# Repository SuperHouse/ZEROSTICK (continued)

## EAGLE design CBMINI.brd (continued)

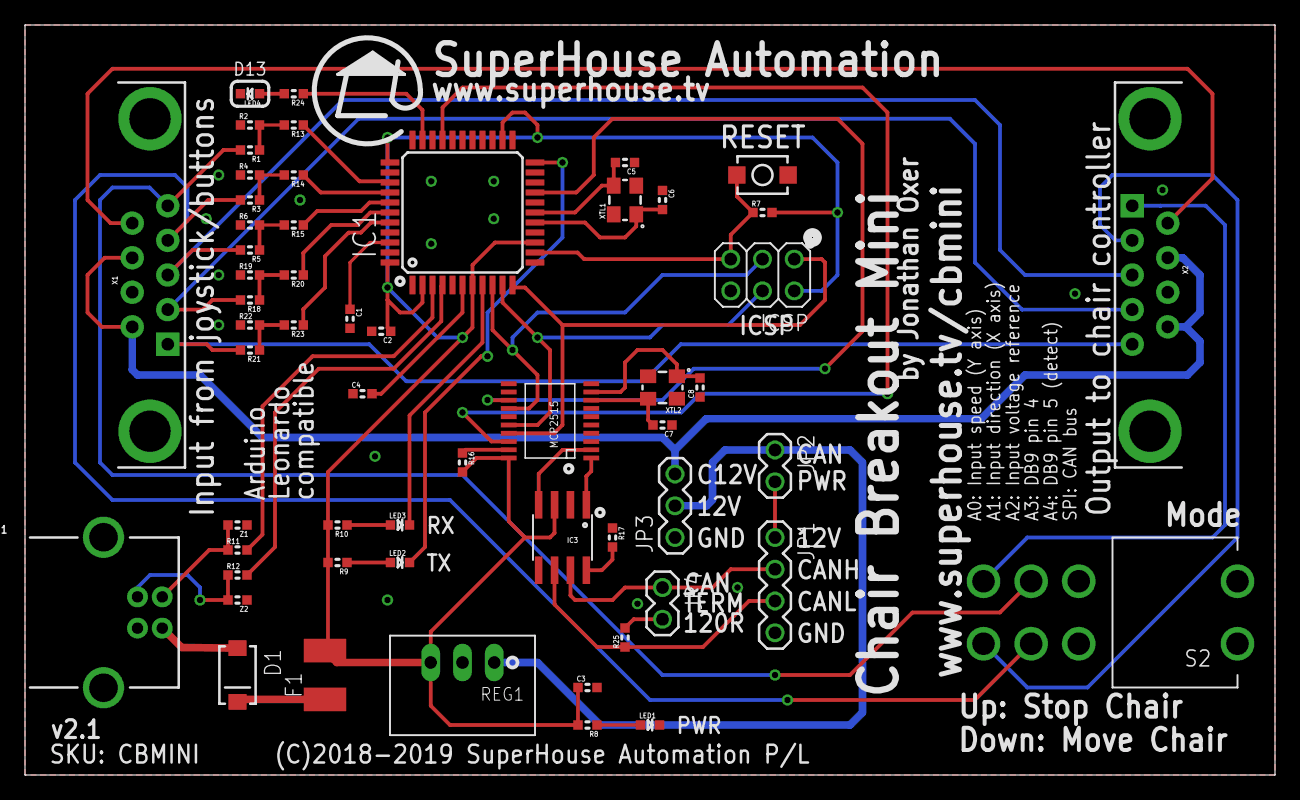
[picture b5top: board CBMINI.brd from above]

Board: 2 copper layers, 100.0 x 60.0 mm, 57 parts (0 on the bottom side), 55 nets.

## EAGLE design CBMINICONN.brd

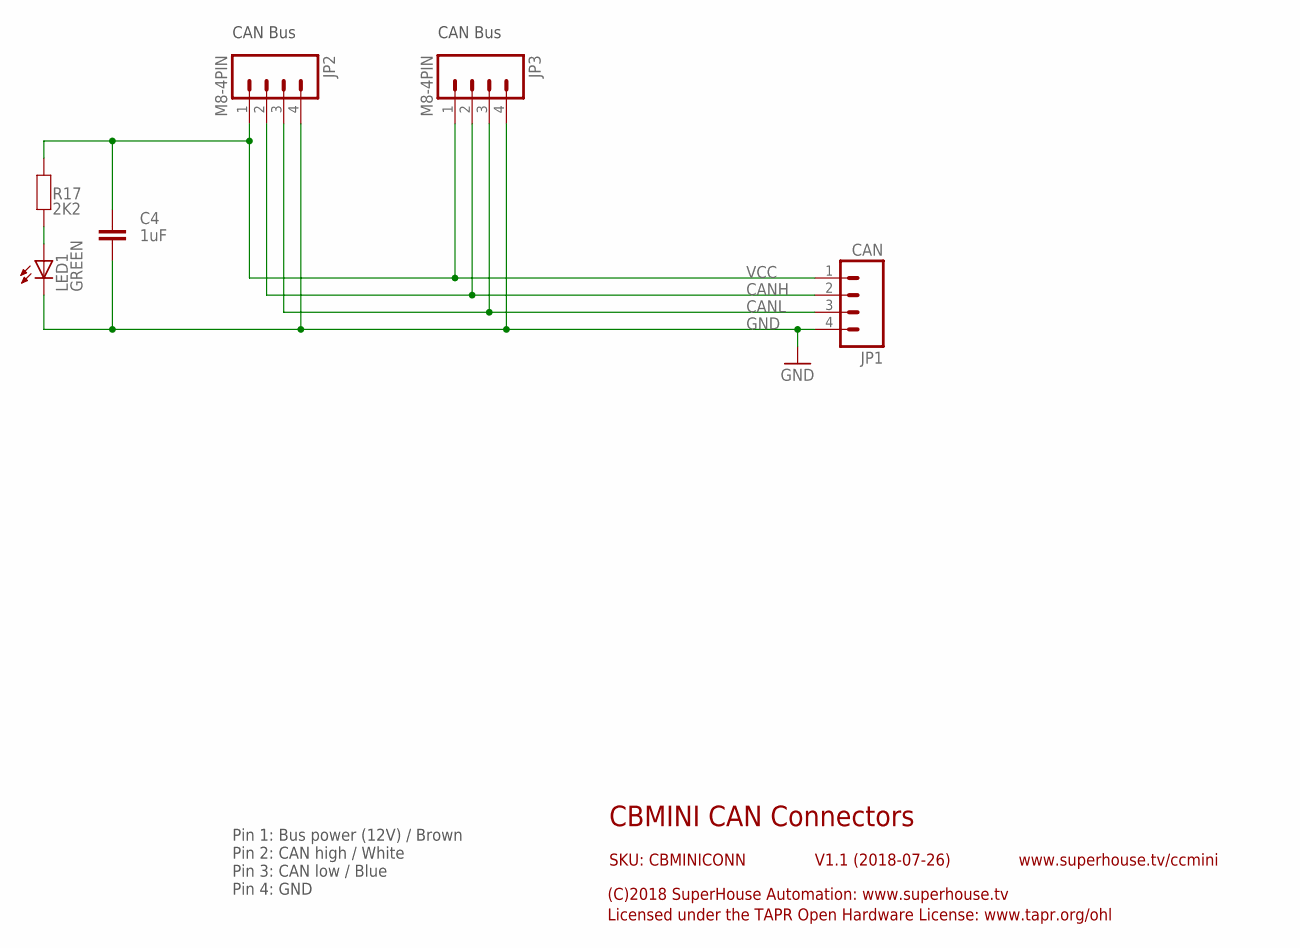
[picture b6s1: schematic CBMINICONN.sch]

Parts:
C4: 1uF; 0603
JP1: CAN; 1X04
JP2, JP3: M8-4PIN
LED1: GREEN; LED3MM
R17: 2K2; 0603

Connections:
CANH: JP1.2, JP2.2, JP3.2
CANL: JP1.3, JP2.3, JP3.3
GND: C4.1, JP1.4, JP2.4, JP3.4, LED1.K (C)
unnamed: LED1.A, R17.1
VCC: C4.2, JP1.1, JP2.1, JP3.1, R17.2

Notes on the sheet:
CBMINI CAN Connectors
V1.1 (2018-07-26)
SKU: CBMINICONN
(C)2018 SuperHouse Automation: www.superhouse.tv
Licensed under the TAPR Open Hardware License: www.tapr.org/ohl
www.superhouse.tv/ccmini
Pin 1: Bus power (12V) / Brown Pin 2: CAN high / White Pin 3: CAN low / Blue Pin 4: GND
CAN Bus

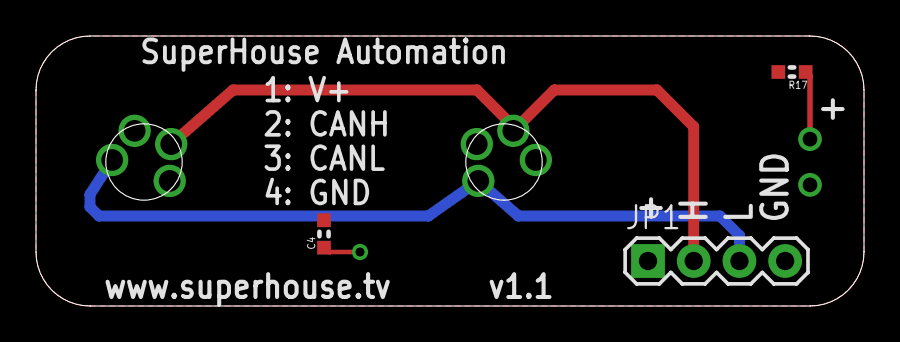
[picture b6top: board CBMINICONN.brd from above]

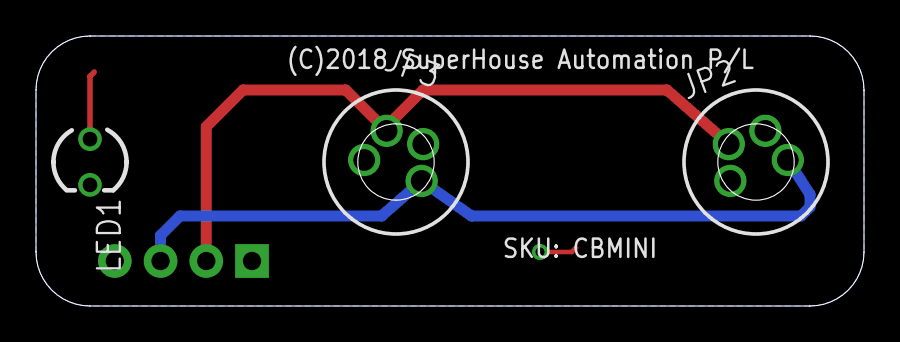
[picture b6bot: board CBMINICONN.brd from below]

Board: 2 copper layers, 46.0 x 15.0 mm, 6 parts (3 on the bottom side), 5 nets.

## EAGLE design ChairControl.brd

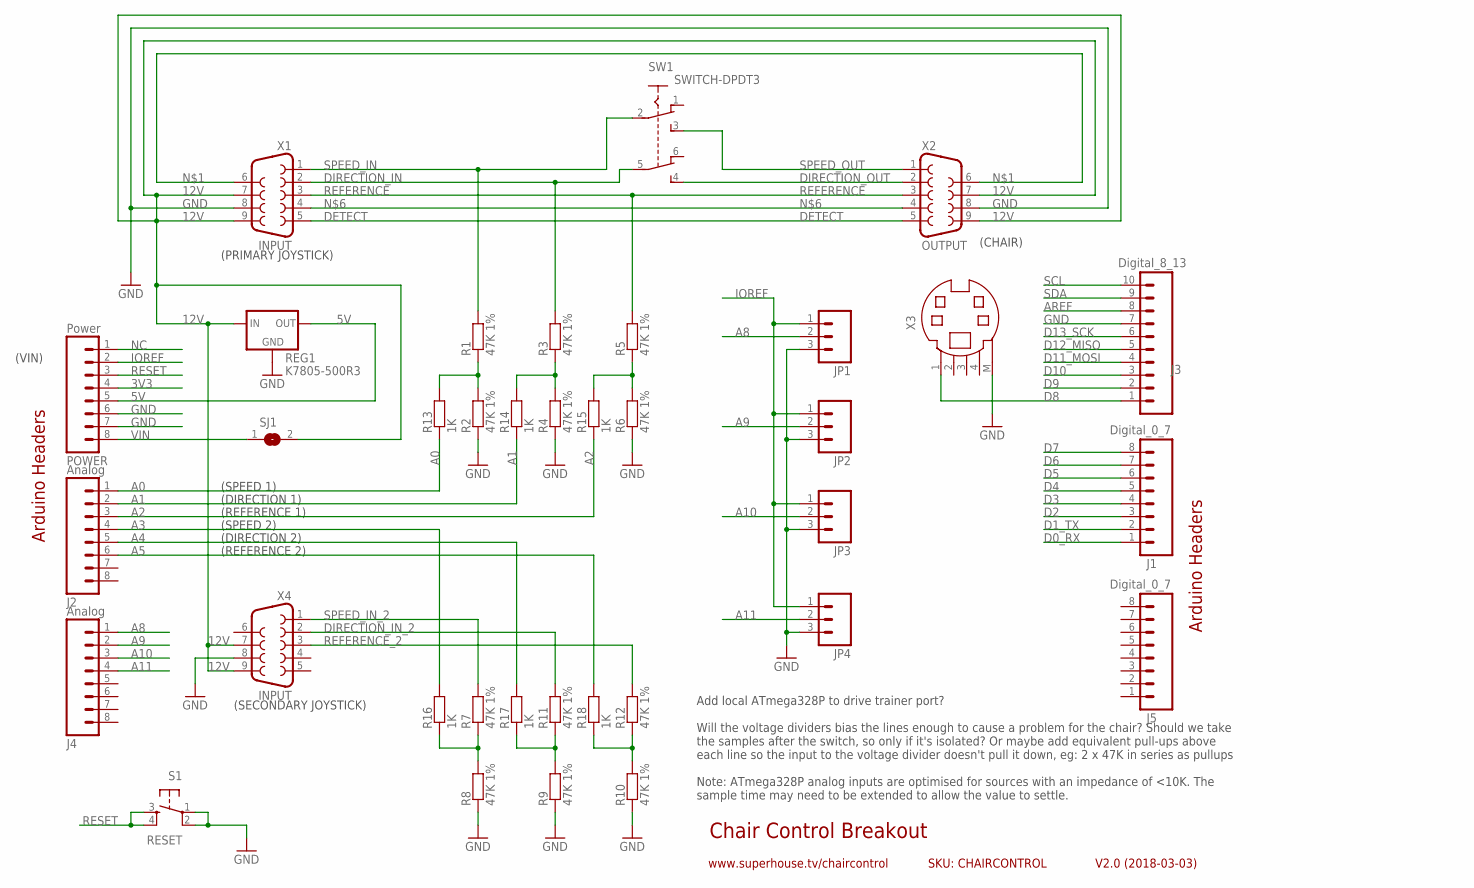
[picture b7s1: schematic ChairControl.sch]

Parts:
J1, J5: Digital_0_7; 1X08
J2, J4: Analog; 1X08
J3: Digital_8_13; 1X10
JP1, JP2, JP3, JP4: M03PTH; 1X03
POWER: Power; 1X08
R1, R2, R3, R4, R5, R6, R7, R8, R9, R10, R11, R12: 47K 1%; 0603
R13, R14, R15, R16, R17, R18: 1K; 0603
REG1: K7805-500R3; K78XX-500R3
S1: RESET; TACTILE-PTH
SJ1: SJN; SJ
SW1: SWITCH-DPDT3; 7201SD9AV2BE
X1, X4: INPUT; DB9_MALE
X2: OUTPUT; DB9
X3: MD04S; MDIN04S

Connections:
3V3: POWER.4
5V: POWER.5, REG1.3 (OUT)
12V: REG1.1 (IN), SJ1.2, X1.7, X1.9, X2.7, X2.9, X4.7, X4.9
A0: J2.1, R13.1
A1: J2.2, R14.1
A2: J2.3, R15.1
A3: J2.4, R16.2
A4: J2.5, R17.2
A5: J2.6, R18.2
A8: J4.1, JP1.2
A9: J4.2, JP2.2
A10: J4.3, JP3.2
A11: J4.4, JP4.2
AREF: J3.8
D0_RX: J1.1
D1_TX: J1.2
D2: J1.3
D3: J1.4
D4: J1.5
D5: J1.6
D6: J1.7
D7: J1.8
D8: J3.1, X3.1
D9: J3.2
D10: J3.3
D11_MOSI: J3.4
D12_MISO: J3.5
D13_SCK: J3.6
DETECT: X1.5, X2.5
DIRECTION_IN: R3.2, SW1.5, X1.2
DIRECTION_IN_2: R11.2, X4.2
DIRECTION_OUT: SW1.4, X2.2
GND: J3.7, JP1.3, JP2.3, JP3.3, JP4.3, POWER.6, POWER.7, R2.1, R4.1, R6.1, R8.1, R9.1, R10.1, REG1.2 (GND), S1.1, S1.2, X1.8, X2.8, X3.M (5), X4.8
IOREF: JP1.1, JP2.1, JP3.1, JP4.1, POWER.2
unnamed: X1.6, X2.6
unnamed: R1.1, R2.2, R13.2
unnamed: R3.1, R4.2, R14.2
unnamed: R5.1, R6.2, R15.2
unnamed: X1.4, X2.4
unnamed: R7.1, R8.2, R16.1
unnamed: R9.2, R11.1, R17.1
unnamed: R10.2, R12.1, R18.1
NC: POWER.1
REFERENCE: R5.2, X1.3, X2.3
REFERENCE_2: R12.2, X4.3
RESET: POWER.3, S1.3, S1.4
SCL: J3.10
SDA: J3.9
SPEED_IN: R1.2, SW1.2, X1.1
SPEED_IN_2: R7.2, X4.1
SPEED_OUT: SW1.3, X2.1
VIN: POWER.8, SJ1.1

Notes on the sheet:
Chair Control Breakout
V2.0 (2018-03-03)
www.superhouse.tv/chaircontrol
SKU: CHAIRCONTROL
Arduino Headers
(PRIMARY JOYSTICK)
(CHAIR)
(VIN)
(SECONDARY JOYSTICK)
Add local ATmega328P to drive trainer port? Will the voltage dividers bias the lines enough to cause a problem for the chair? Should we take the samples after the switch, so only if it's isolated? Or maybe add equivalent pull-ups above each line so the input to the voltage divider doesn't pull it d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
(SPEED 1)
(SPEED 2)
(DIRECTION 1)
(DIRECTION 2)
(REFERENCE 1)
(REFERENCE 2)

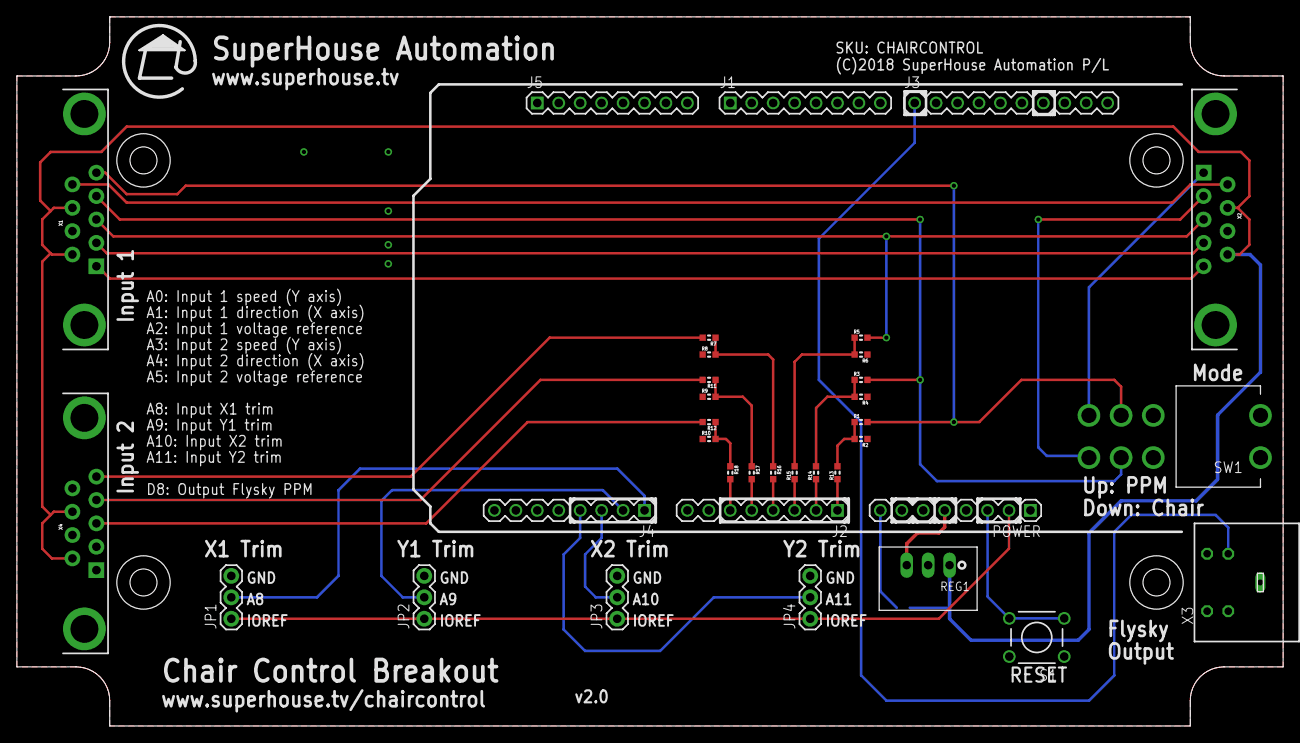
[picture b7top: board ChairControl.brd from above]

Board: 2 copper layers, 150.0 x 84.0 mm, 36 parts (1 on the bottom side), 34 nets.

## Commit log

2018-02-06 Initial project import
2018-02-06 Added Mini DIN-4 connector for Flysky trainer cable connection
2018-02-07 Added second joystick input and changed outline to suit HB5922 case
2018-02-07 Moved Arduino headers to correct location and adjusted connector positions
2018-02-08 Routing and silkscreen
2018-02-08 Added README
2018-02-08 DRC and generated gerbers for v1.0 release
2018-03-03 Added trim inputs and extra headers for Mega footprint
2018-03-27 Improved silkscreen
2018-07-10 Isolated 12V power from passthrough to allow separate power source
2018-07-10 Forked project files for Mini version
2018-07-10 Added CAN interface and removed second joystick input
2018-07-12 Added power source selection and DRC for v1.0 release
2018-07-18 Renamed project files to match SKU
2018-07-23 Improved designators
2018-07-26 Added CAN bus interrupt connection to D2 for v1.1 release
2018-07-27 Changed CAN crystal to 16MHz for compatibility with Arduino CAN shields
2018-07-27 Added connector header board
2019-04-11 Added extra input channels and CAN termination for v2.0 release
2019-04-17 Improved value labels
2019-04-23 Changed input 5 to pin 5 for v2.1 release
2019-06-18 Removed 120R termination, rotated connectors by 20 degrees, and added circular cut-out
2019-08-30 Clearance for connectors
2019-11-13 Clickety click, replace replace
2019-11-13 Restructured voltage regulators to support 24V CAN or Permobil controller for v2.2 release
2019-12-05 File renaming
2019-12-05 Basic schematic done and rough board outline
2019-12-08 Replaced pot with rotary encoder, switched input and output sides
2019-12-10 Big cleanup of routing and silkscreen, with updated 3D model for OLED
2019-12-10 Replaced RJ10 socket with RJ12 and added haptic feedback output
2019-12-10 Routing for haptic feedback
2019-12-10 Added render
2019-12-10 Fixed image name
2019-12-19 ERC / DRC for v1.0 release
2019-12-19 Tweaks and cleanup, hopefully for v1.1 release
2020-02-13 Added HX711 strain gauge amplifier directly on controller instead of external
2020-02-13 Routing for v2.0 release
2020-03-17 Synch with Fusion 360
2020-04-30 Added mounting holes for v2.1 release
2020-05-08 Added Tare button and beep stretch switch, still for v2.1 release
2020-05-12 Removed haptic feedback and changed to RJ10 connector for v3.0 release
2020-05-12 Still for v3.0 release: updated design rules and improved clearances
2020-05-12 Added stencil DXF for v3.0
2020-06-25 Renamed project files from SuperButton
2020-06-30 Resized images
2020-07-02 Added mouse buttons and changed load cell readings to interrupt driven
2020-07-06 Partical conversion from SB project
2020-07-09 Changed sensitivity scaling
2020-07-09 Reversed axis directions, and fixed tare function
2020-07-14 Start of restructuring project
2020-07-14 Added licenses
2020-07-14 Moved hardware files into subdirectory
2020-07-14 Added image to README
2020-07-14 Fixed directory name
2020-12-02 Added WIP PCB for load cell interface.
2020-12-02 Added .gitignore.
2020-12-08 New version of load cell interface with only 1 x NAU7802.
2020-12-08 Added datasheets for NAU7892 and TCA9548A.
2020-12-08 Partial conversion of early concept PCB.
2020-12-08 Experiments with firmware for ATTiny.
2020-12-08 Added preview image of ZSLC PCB.
2021-01-12 Renamed firmware and forked to create an alternative version for NAU7802.
2021-01-12 Removed old files.
2021-01-12 Converted firmware to use NAU7802. Fixed HID emulation for bouse button events on Leonardo.
2021-02-01 Added images of previous and current prototype connections.
2021-03-29 Added ESP32 version of firmware.
2021-03-30 Matched schematic input channel labels to PCB silkscreen.
2021-03-30 Added firmware to test a single NAU7802.
2021-03-30 Added firmware tests for ESP32 and NAU7802.
2021-03-30 More firmware experiments.
2021-04-06 Fixed labels and values on X and Y axis connectors.
2021-04-06 Added firmware version that uses MUX. Added MedianAverage rolling buffer. Added manual zero offset. Added center dead spot. Scaled reading to fit within +/-100 range.
2021-04-09 Changed mouse button input pin assignments. Added debugging to show mouse button emulation mode.
2021-04-13 Removed obsolete references to I2C multiplexer.
2021-04-13 Apply scaling and range limiting to digipot outputs. Swap X and Y axis digipot I2C addresses to match CHAIRI2C board. Add separate debugging flags for different purposes.
2021-04-13 Fixed capitalisation of directory.
2021-04-13 Added explanation of example firmware features.
2021-04-13 Added config option for digipot output speed. Added config option for full scale rating on load cells. Added config option for effort required for full scale deflection. Added config option for load 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
2021-04-13 Removed temporary debugging line.
2021-04-20 Moved digipot center position from 63 to 65 to compensate for offset. Inverted digipot X and Y axes to match Permobil inputs. Constrained digipot output range to +/-15.
2021-04-20 Added video of controlling Permobil wheelchair.
2021-05-07 Add configuration option to set wheelchair control center position.
2021-05-07 Make all three output methods selectable. Changed to using fork of joystick library to support SAMD21 Conditional library includes based on target architecture. Added information about libraries and 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
2021-05-07 Reverse joystick output directions and match scale to inputs.
2021-05-11 Change name of gamepad emulation to gamepad. When in gamepad mode, use the mouse button inputs as gamepad button inputs. Define gamepad with 2 buttons.
